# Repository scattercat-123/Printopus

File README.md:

# Printopus
The ultimate 3d printer was built by me.
Open the journey over here - [Printopus-Journey.md](Printopus-Journey.md)

## What I plan to add to the printer which is special from others!
<ul>
  <li>Filament run out sensor</li>
  <li>Custom lighting under the extruder</li>
  <li>Since most of the printers are mostly like a machine which has to just print things I am planning to add a user interactive game in the printer itself with the touchscreen!</li>
  <li>Automatic nozzle cleaner with silicone pads</li>
</ul>

## Extras!!

<i>Random photos of the journey!!</i>

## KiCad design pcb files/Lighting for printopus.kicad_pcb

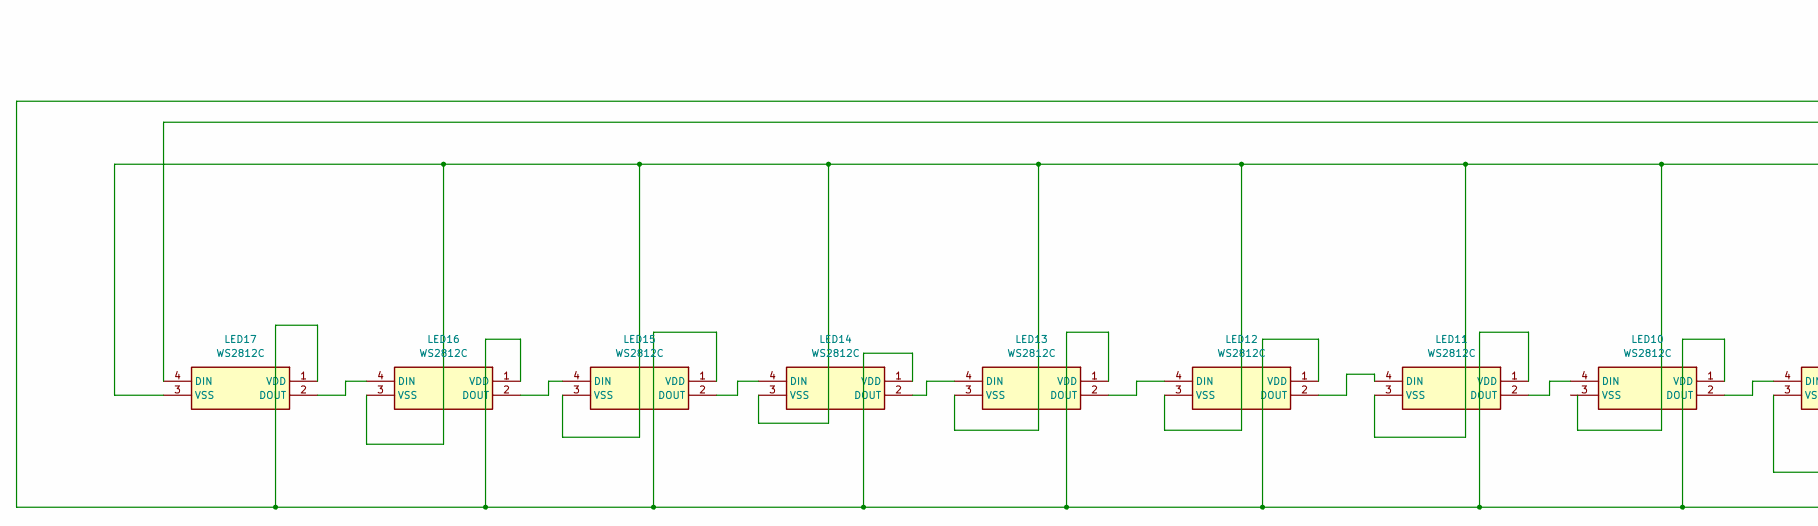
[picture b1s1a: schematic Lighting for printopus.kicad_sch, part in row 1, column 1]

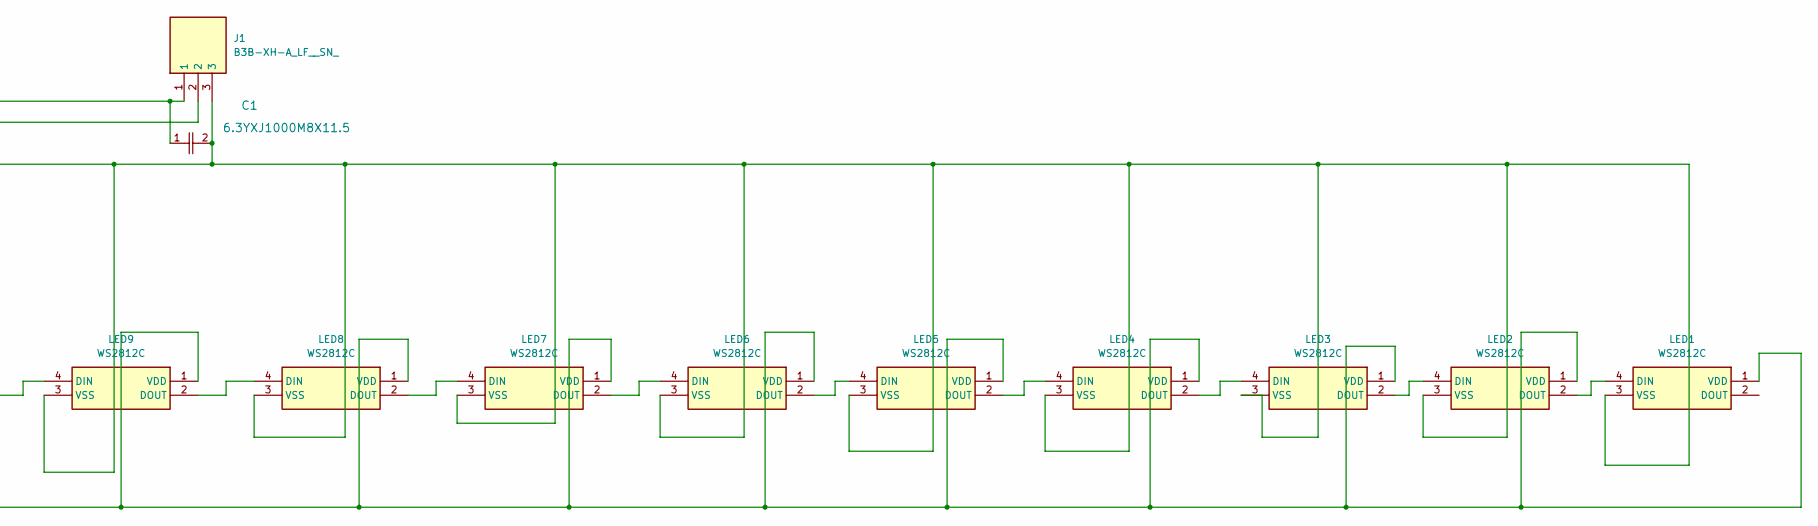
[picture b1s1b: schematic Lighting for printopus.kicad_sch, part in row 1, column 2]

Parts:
C1: 6.3YXJ1000M8X11.5; CAP_YX_8X11P5_RUB
J1: B3B-XH-A_LF__SN_; B3BXHALFSN; Manufacturer_Part_Number B3B-XH-A(LF)(SN); Mouser Part Number 306-B3BXHALFSNP
LED1, LED2, LED3, LED4, LED5, LED6, LED7, LED8, LED9, LED10, LED11, LED12, LED13, LED14, LED15, LED16, LED17: WS2812C; Manufacturer_Part_Number WS2812C

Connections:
unnamed: LED1.4 (DIN), LED2.2 (DOUT)
unnamed: C1.1, J1.1, LED1.1 (VDD), LED2.1 (VDD), LED3.1 (VDD), LED4.1 (VDD), LED5.1 (VDD), LED6.1 (VDD), LED7.1 (VDD), LED8.1 (VDD), LED9.1 (VDD), LED10.1 (VDD), LED11.1 (VDD), LED12.1 (VDD), LED13.1 (VDD), LED14.1 (VDD), LED15.1 (VDD), LED16.1 (VDD), LED17.1 (VDD)
unnamed: C1.2, J1.3, LED1.3 (VSS), LED2.3 (VSS), LED3.3 (VSS), LED4.3 (VSS), LED5.3 (VSS), LED6.3 (VSS), LED7.3 (VSS), LED8.3 (VSS), LED9.3 (VSS), LED11.3 (VSS), LED12.3 (VSS), LED13.3 (VSS), LED14.3 (VSS), LED15.3 (VSS), LED16.3 (VSS), LED17.3 (VSS)
unnamed: LED2.4 (DIN), LED3.2 (DOUT)
unnamed: LED3.4 (DIN), LED4.2 (DOUT)
unnamed: LED4.4 (DIN), LED5.2 (DOUT)
unnamed: LED5.4 (DIN), LED6.2 (DOUT)
unnamed: LED6.4 (DIN), LED7.2 (DOUT)
unnamed: LED7.4 (DIN), LED8.2 (DOUT)
unnamed: LED8.4 (DIN), LED9.2 (DOUT)
unnamed: LED10.4 (DIN), LED11.2 (DOUT)
unnamed: LED9.4 (DIN), LED10.2 (DOUT)
unnamed: LED11.4 (DIN), LED12.2 (DOUT)
unnamed: LED12.4 (DIN), LED13.2 (DOUT)
unnamed: LED13.4 (DIN), LED14.2 (DOUT)
unnamed: LED14.4 (DIN), LED15.2 (DOUT)
unnamed: LED15.4 (DIN), LED16.2 (DOUT)
unnamed: LED16.4 (DIN), LED17.2 (DOUT)
unnamed: J1.2, LED17.4 (DIN)

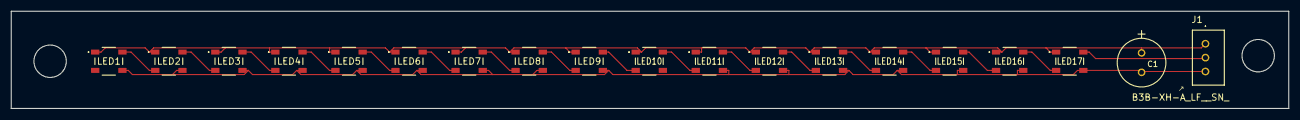
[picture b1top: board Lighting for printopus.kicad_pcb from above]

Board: 2 copper layers, 230.0 x 17.5 mm, 19 parts (0 on the bottom side), 19 nets.

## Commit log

2025-02-13 Add the basic format and 1st day to the journey!
2025-02-13 addded more things for day 1 i am very stupid
2025-02-13 I am so dumb i wrote "day 2" instead of day 1 bruh what the skibidi
    bruh
2025-02-14 day 2 (going to sleep will complete journal tmrw)
2025-02-15 Updated day 2 and couldnt do day 3
2025-02-16 Make the Readme better
2025-02-16 Updated Day 4 with fever :(
2025-02-16 Just some final touched to day4
2025-02-17 Fixed README.md
2025-02-17 Day 5 I still have High Fever 🤒
2025-02-17 added extras
2025-02-19 day 6?
2025-02-23 Added img
2025-03-14 Finally good update
2025-03-28 14 days updated i think its major one
2025-04-02 Skibidi Printopus Journey
2025-04-02 Skibidi info with important link
2025-04-02 cad files added
2025-04-04 Yeah last update sorry for skibidi grammar
2025-04-04 added pcb files
2025-04-04 Skibidi journey
2025-04-04 Create frame
2025-04-04 organized files
2025-12-18 Updated Printopus journal with build pics
